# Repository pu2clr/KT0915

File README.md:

# [PU2CLR KT0915 Arduino Library](https://pu2clr.github.io/KT0915/)

This is an Arduino Library to control the KT0915 DSP receiver from KTMicro. The KT0915 is an integrated circuit that provides full band receiver on FM and AM (MW/SW/LW).

[Copyright (c) 2020 Ricardo Lima Caratti](https://pu2clr.github.io/KT0915#mit-license).

Contact: __pu2clr@gmail.com__.

__If you find this project useful, consider making a donation so that the author can purchase components and modules for improvements and testing of this library.__
[Click here to donate](https://www.paypal.com/donate/?business=LLV4PHKTXC4JW&no_recurring=0&item_name=Consider+making+a+donation.++So+I+can+purchase+components+and+modules+for+improvements+and+testing+of+this+library.&currency_code=USD)

## About Me

I hold a Master's degree in Educational Technology from the Federal University of Ceará, where I delved into the ways technology can enhance learning experiences. My passion for computer science led me to specialize in it, focusing on Distributed Systems Development with an Object-Oriented approach, at the University of Brasília. My academic journey began with a Bachelor's degree in Information Systems from the União Pioneira de Integração Social (UPIS-Brasília). Outside the classroom, my main hobbies are electronics and Amateur Radio. 

Be a member of Facebook group [DSP receivers for hobbyists](https://www.facebook.com/groups/2655942598067211)

## Donate 

If you find this project useful, consider making a donation so that the author of this library can purchase components and modules for improvements and testing of this library. [Click here to donate.](https://www.paypal.com/donate/?business=LLV4PHKTXC4JW&no_recurring=0&item_name=Consider+making+a+donation.++So+I+can+purchase+components+and+modules+for+improvements+and+testing+of+this+library.&currency_code=USD)

# Contents

1. [Preface](https://pu2clr.github.io/KT0915#preface)
2. [Your support is important](https://pu2clr.github.io/KT0915#your-support-is-important)
3. [Library Features](https://pu2clr.github.io/KT0915#library-features)
4. [MIT License](https://pu2clr.github.io/KT0915#mit-license)
5. [Library Installation](https://pu2clr.github.io/KT0915#library-installation)
6. [About KT0915 DSP radio](https://pu2clr.github.io/KT0915#about-kt0915-dsp-radio)
   * [KT0915 pinout](https://pu2clr.github.io/KT0915#kt0915-pinout)
7. [SCHEMATIC](https://pu2clr.github.io/KT0915#schematic)
8.  [API Documentation](https://pu2clr.github.io/KT0915/extras/docs/html/index.html)
9.  [Source code - Examples](https://github.com/pu2clr/KT0915/tree/master/examples)
10. [Videos](https://pu2clr.github.io/KT0915#videos)
11. [References](https://pu2clr.github.io/KT0915#references)

## Preface

The KT0915 is a full band AM (LW, MW and SW) and FM DSP receiver that can provide you a easy way to build a high quality radio with low cost. This device, will surprise hobbyists and experimenters with its simplicity.

In this document you will see Arduino source codes, schematics, examples and tips to help you to build a receiver based on Arduino board and the KT0915 device.  The project and examples shown here do not intend to be a real receiver for exigent listener. However, it is possible to start with it and after add some improvements. On the other hand, with the simple circuits shown here, the experimenter may be surprised with its performance.

{% include video01.html %}

[PU2CLR KT0915 Arduino LIbrary - AM (MW and SW) and FM receiver with KT0915](https://youtu.be/H6SwbuN3niU)

<BR>

{% include tutorial.html %}

[Video Tutorial](https://youtu.be/f3P6KL0XJpw)

## See also

* [PU2CLR Si4735 Library for Arduino](https://pu2clr.github.io/SI4735/). This library was built based on “Si47XX PROGRAMMING GUIDE; AN332” and it has support to FM, AM and SSB modes (LW, MW and SW). It also can be used on all members of the SI47XX family respecting, of course, the features available for each IC version;
* [PU2CLR SI4844 Arduino Library](https://pu2clr.github.io/SI4844). This is an Arduino library for the SI4844, BROADCAST ANALOG TUNING DIGITAL * DISPLAY AM/FM/SW RADIO RECEIVER,  IC from Silicon Labs.  It is available on Arduino IDE. This library is intended to provide an easier interface for controlling the SI4844.
* [PU2CLR AKC695X Arduino Library](https://pu2clr.github.io/AKC695X/). The AKC695X is a family of IC DSP receiver from AKC technology. The AKC6955 and AKC6959sx support AM and FM modes. On AM mode the AKC6955 and AKC6959sx work on LW, MW and SW. On FM mode they work from 64MHz to 222MHz.
* [PU2CLR KT0915 Arduino Library](https://pu2clr.github.io/KT0915/). The KT0915 is a full band AM (LW, MW and SW) and FM DSP receiver that can provide you a easy way to build a high quality radio with low cost.
* [PU2CLR BK108X](https://pu2clr.github.io/BK108X/). The BK1086 and BK1088 are DSP receivers from BAKEN. The BK1088 is a BROADCAST FM and AM (LW, MW and ) RECEIVER and BK1086 is a subset of the BK1088 (it does not have LW and SW acording to the Datasheet).
* [PU2CLR RDA5807 Arduino Library](https://pu2clr.github.io/RDA5807/). The RDA5807 is a FM DSP integrated circuit receiver (50 to 115MHz) with low noise amplifier support. This device requires very few external components if compared with other similar devices. It also supports RDS/RBDS functionalities, direct auto gain control (AGC) and real time adaptive noise cancellation function.
* [PU2CLR SI470X Arduino Library](https://pu2clr.github.io/SI470X/). It is a Silicon Labs device family that integrates the complete functionalities for FM receivers, including RDS (Si4703).
* [PU2CLR MCP23008](https://pu2clr.github.io/MCP23008/). It is an Arduino Library to control the MCP23008/MCP23S08 8-Bit I/O Expander. The MCP23008 device provides 8-bit, general purpose, parallel I/O expansion. It can be controlled via I2C bus applications. It is a great and inexpensive device that allow you to add more devices to be controlled by your Arduino board via I2C protocol.
* [PU2CLR - PCF8574 Arduino Library](https://pu2clr.github.io/PCF8574/). It is an Arduino Library to control the PCF8574 8-Bit I/O Expander. The PCF8574 device provides 8-bit, general purpose, parallel I/O expansion. It can be controlled via I²C bus applications. It is a great and inexpensive device that allow you to add more peripherals to be controlled by your Arduino board via I²C protocol.
* [QN8066 FM DSP RX/TX Arduino Library](https://github.com/pu2clr/QN8066). An easy-to-use interface for controlling the QN8066 FM transceiver and receiver.

### More Arduino Projects developed by author 

* [Multipurpose signal generator with SI5351](https://pu2clr.github.io/SI5351/). It is a multipurpose signal generator controlled by Arduino. This project uses the SI5351 from Silicon Labs. The Arduino sketch is configured to control the SI5351 with three channels from 32.768KHz to 160MHz and steps from 1Hz to 1MHz.
* [Shortwave Arduino Transmitter](https://pu2clr.github.io/Small-Shortwave-Transmitter/). This project is about a shortwave transmitter from 3 MHz to 30 MHz. It uses the SI5351 oscillator from Silicon Labs controlled by Arduino. Also, you can use it with a crystal oscillator. In this case, you will not need the SI5351 device and Arduino. 
* [Android and iOS Bluetooth Remote Control for PU2CLR Arduino Library DSP receivers](https://pu2clr.github.io/bluetooth_remote_control/). This project is an extension of the Arduino library projects for: [SI4735](https://pu2clr.github.io/SI4735/); [AKC6959](https://pu2clr.github.io/AKC695X/) and [KT0915](https://pu2clr.github.io/KT0915/). It is a simple example that shows a way to use your smartphone as a remote control via Bluetooth. In order to follow the steps presented here, I am assuming that you have some knowledge in development for mobile devices. Also, you will need to be familiar with the Javascript programming language. The development environment used by this project is the [Apache Cordova](https://cordova.apache.org/docs/en/latest/guide/overview/index.html). Cordova is a open-source mobile development framework that allows you to develop cross-platform applications. That means you can code once and deploy the application in many system, including iOS and Android. 
Cordova provides an easy way to develop for iOS and Android.  
* [Band Pass Filter controlled by Arduino](https://pu2clr.github.io/auto_bpf_arduino/). It is a HF band pass filter controlled by Arduino. It is designed for HF receivers. With this project, you can use a set of up to four HF bandpass filters that can be selected by Arduino. To do that you will need just two digital Arduino pins.

## Your support is important

If you would like to support this library development, consider joining this project via Github. Alternatively, make suggestions on new features and report errors if you find them. Thank you!

## Library Features

This library uses the I²C communication protocol and implements most of the functions offered by the KT0915 (BROADCAST AM / FM / SW / LW RECEIVER).

The main features of this library are listed below.

1. Open Source. It is free. You can use, copy, modify, merge, publish, distribute, sublicense, and/or sell copies of the Software. See [MIT License to know more](https://pu2clr.github.io/AKC695X/#mit-license);
2. Built based on [KT0915 stereo FM / TV / MW / SW / LW digital tuning radio](http://maximradio.altervista.org/akc6955/AKC6955-datasheet-english.pdf);
3. C++ Language and Object-oriented programming. You can easily extend the AKC695X class by adding more functionalities;
4. Available on Arduino IDE (via Manage Libraries). Easy to install and use;
5. Cross-platform. You can compile and run this library on most of board available on Arduino IDE (Examples: ATtiny85, boards based on ATmega328 and ATmega-32u4, ATmega2560, ARM Cortex, STM32, Arduino DUE, ESP32 and more);
6. Simplifies projects based on KT0915 IC;
7. Support to 32.768KHz and external reference clock;
8. Support to audio controlled by the MCU (Arduino)  or potentiometer;
9.  Real time FM stereo or mono indicator;
10. FM stereo or mono selecting;
11. Real time signal level reading;
12. Real time AM and FM carrier to noise ratio information (dB).
13. Bandwidth selection for AM;
14. Custom band support;
15. More than 40 functions implemented.

## MIT License

Copyright (c) 2019 Ricardo Lima Caratti

Permission is hereby granted, free of charge, to any person obtaining a copy of this software and associated documentation files (the "Software"), to deal in the Software without restriction, including without limitation the rights to use, copy, modify, merge, publish, distribute, sublicense, and/or sell copies of the Software, and to permit persons to whom the Software is furnished to do so, subject to the following conditions:

The above copyright notice and this permission notice shall be included in all copies or substantial portions of the Software.

THE SOFTWARE IS PROVIDED "AS IS", WITHOUT WARRANTY OF ANY KIND, EXPRESS OR IMPLIED, INCLUDING BUT NOT LIMITED TO THE ARRANTIES OF MERCHANTABILITY, FITNESS FOR A PARTICULAR PURPOSE AND NONINFRINGEMENT. IN NO EVENT SHALL THE AUTHORS OR COPYRIGHT HOLDERS BE LIABLE FOR ANY CLAIM, DAMAGES OR OTHER LIABILITY, WHETHER IN AN ACTION OF CONTRACT, TORT OR OTHERWISE, ARISING FROM, OUT OF OR IN CONNECTION WITH THE SOFTWARE OR THE USE OR OTHER DEALINGS IN THE SOFTWARE.

<BR>

## Library Installation

You can install this library on your Arduino environment using different methods. The best ways to do that are described below.  

{% include libinstalling.html %}

### Installing via Arduino IDE

// TODO

## About KT0915 DSP radio

According to __"Monolithic Digital FM/MW/SW/LW Receiver Radio on a Chip(TM); KT0915"__ document from KTMicro, "the KT0915 is a fully integrated full band AM/FM digital radio receiver IC with patented technologies that offer full band FM/MW/SW/LW functionality, high quality audio performance, simple design and low BOM cost.
The direct frequency and volume control interface help custumers to maintain the classic looks of their existing products.

Thanks to the patented tuning technology, the receiver maintains good signal reception with short antenna. The chip consumes only 22mA current and can be powered by 2 AAA batteries. Another useful feature is that the volume and channel setup can be preserved in standby mode without external memories. KT0915 supports a wide range of reference clocks from 32.768KHz to 26MHz, hence can share system clocks with a varieties of MCUs further reducing the system BOM cost.

With high audio performance, fully integrated features and low BOM cost, KT0915 is ideal for various FM/MW/SW/LW applications and products".

### KT0915 features

1. Worldwide full band FM/MW/SW/LW support FM: 32MHz-110MHz
   * FM: 32MHz-110MHz
   * MW: 500KHz-1710KHz 
   * SW: 1.6MHz~32MHz 
   * LW: 150KHz ~ 280KHz
2. Fully integrated frequency synthesizer with no external component
3. High Sensitivity
   * 1.6uVEMF for FM
   * 16uVEMF for AM
4. High Fidelity
   * SNR (FM/AM): 60dB/55dB
   * THD: 0.3%
5. Low supply voltage: 2.2V to 3.6V, can be supplied by 2 AAA batteries
6. Automatic antenna tuning
7. Adjustable AM channel filters (2k/4k/6KHz)
8. Embedded FM SNR meter
9.  Fast seek/Tune
10. Integrated stereo headphone driver I²C control interface for MCU
11. Support traditional dial and digital key for frequency tuning and volume control
12. Memorize channel and volume in standby mode
13. Low Supply Current - 22mA (operating) <15uA (standby)
14. Support both 32.768KHz and 38KHz crystal
15. Support continuous reference frequency from 32.768KHz to 26MHz

Source: __"Monolithic Digital FM/MW/SW/LW Receiver Radio on a Chip(TM); KT0915"__ document from KTMicro

### KT0915 Pinout

 | Pin Number  | Pin Name  | Description |
 | ----------  | --------  | ----------- |
 | 1           | CH        | Channel Adjustment. Used to deal with mechanical tune option |
 | 2           | DVSS      | Digital Ground |
 | 3           | ROUT      | Righ channel audio output |
 | 4           | LOUT      | Left channel audio output |
 | 5           | AVSS      | Analog ground |
 | 6           | AVDD      | Power Supply |
 | 7           | XI/RCLK   | Crystal input or reference clock input setup |
 | 8           | XO        | Crystal Output |
 | 9           | ENABLE    | Chip enable. Tied to an internal 600kohm pull down resistor |
 | 10          | AMINN     | AM RF negative input |
 | 11          | AMINP     | AM RF positive input |
 | 12          | RFINP     | FM RF input |
 | 13          | RFGND     | RF ground |
 | 14          | SCL       | SCL of I²C bus. Tied to an internal 47kohm pull-up resistor |
 | 15          | SDA       | SDA of I²C bus. Tied to an internal 47kohm pull-up resistor |
 | 16          | VOL       | Volume adjustment. Used to deal with mechanical volume control |

### KT0915 SSOP16L package

#### About the Pin 1 (CH) and Pin 16 (VOL)

The KT0915 can be configured to deal with mechanical tuning via a variable resistors. For example, you can use a variable resistor to control the audio volume and another to tuninig the receiver. This resource is  enabled by setting the internal register GPIOCFG (Address 0x1D) of the device. The dial can be a variable resistor with the tap connected to CH and VOL as well. The divided voltage at the tap is processed by the internal KT0915  analog to digital converter (ADC). Finally, the converted datas are stored into the internal registers of the KT0915 device.

By default, this library the tune and volume are conttrolled by the MCU (Arduino). However, you can sets the mechanical feature by calling setTuneDialModeOn and setVolumeDialModeOn. See [API Documentation](https://pu2clr.github.io/KT0915/extras/docs/html/index.html).

See [KT0915 - Monolithic Digital FM/MW/SW/LW ReceiverRadio-on-a-Chip™](http://aitendo3.sakura.ne.jp/aitendo_data/product_img/ic/radio/KT0915%20/KT0915_datasheet_V022_aitendo.pdf); pages: 8, 9, 10 and 20.

## SCHEMATIC

You can use the Typical Application Circuit suggested by the KTMicro. This circuit can be found in the document KT0915-Monolithic Digital FM/MW/SW/LW Receiver Radio-on-a-Chip.  The main porpuse of this prototype below is testing de KT0915 Arduino Library. It does not intend to be a real radio for exigent listener. However, it is possible to start with it and after include some devices to improve, for example,  its sensibility beyond other desired features.  The schematic below does not use the ferrite antenna as suggested by KTMicro and no front-en as well.  See [KT0915 - Monolithic Digital FM/MW/SW/LW ReceiverRadio-on-a-Chip™](http://aitendo3.sakura.ne.jp/aitendo_data/product_img/ic/radio/KT0915%20/KT0915_datasheet_V022_aitendo.pdf); page 24.

<BR>

<BR>

__The KT0915 is a 3.3V part. If you are not using a 3.3V version of Arduino, you have to use a kind of 5V to 3.3V bidirectional converter. It is important to say that just power the KT0915 device with 3.3V from Arduino board is not enough. You have to be aware that the Arduino that operates with 5V, the digital pins and the I²C bus will send 5V signals to the KT0915 device. That configuration can make the system unstable or damage the device__.  

### Parts

The table below shows the component parts used to build the receiver prototype based on KT0915

<BR>

| Components |  Value    | Description |
| ---------- |  -------- | ----------- |
|    C1      |  10uF     | Ceramic or tantalum capacitor |
|    C2      |  100nF    | Ceramic or tantalum capacitor |
|   C3, C4   |  22pF     | Supply decoupling capacitor - Ceramic or tantalum capacitor |
|   C5, C6   |  10uF     | Electrolytic or tantalum capacitor |
|    C7      |  100nF    | AC coupling capacitor |  
|    Q1      | 32.768KHz | Crystal |
|   R1, R2   |  10K      | I²C buss Pull up ristors |
|   Arduino  | Pro Mini  | 3.3V 8Mhz |
|   KT0915   | DSP       | FM and AM receiver |
|    VCC     | 3.3V      | Baterry |

<BR>

## Photos

<BR>

<BR>

## Videos

[PU2CLR KT0915 Arduino LIbrary - First Test](https://youtu.be/H6SwbuN3niU)
[PU2CLR KT0915 Arduino Library - Sound testing](https://youtu.be/L3R1hmw8tqg)

## References

* [KT0915 - Monolithic Digital FM/MW/SW/LW ReceiverRadio-on-a-Chip™](http://aitendo3.sakura.ne.jp/aitendo_data/product_img/ic/radio/KT0915%20/KT0915_datasheet_V022_aitendo.pdf)
* [Radio, yes AM-SW-FM radio by DSP radio chip](https://hackaday.io/project/12944-radio-yes-am-sw-fm-radio-by-dsp-radio-chip)
* [KT0915_DSP_RADIO-fullscreen-info](https://github.com/kodera2t/KT0915_DSP_RADIO-fullscreen-info)
* [KT0915 Arduino](https://easyeda.com/wolfezrawilliam/KT0915-Arduino)

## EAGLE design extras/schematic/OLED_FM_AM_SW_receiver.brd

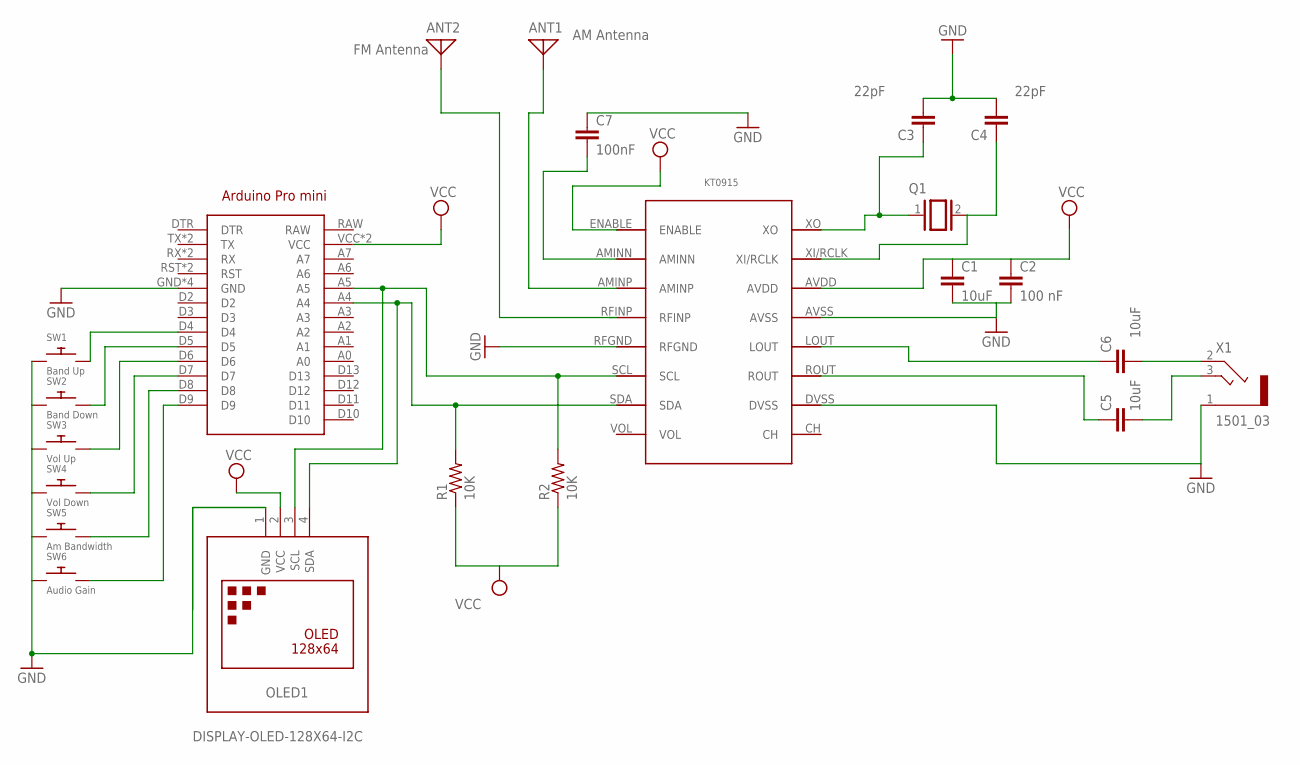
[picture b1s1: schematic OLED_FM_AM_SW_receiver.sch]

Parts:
ANT1: AM Antenna; PAD-01
ANT2: FM Antenna; PAD-01
ARDUINO1: ProMini 3.3v 8MHz; ARDUINO_PRO_MINI
C1: 10uF; 0603
C2: 100 nF; C1825K
C3, C4: 22pF; C1825K
C5, C6: 10uF; C1825K
C7: 100nF; C1825K
KT0915: KT0915
OLED1: DISPLAY-OLED-128X64-I2C
Q1: XTAL; Q
R1, R2: 10K; 0805-THM
SW1: Band Up; TACT_PANA-EVQ
SW2: Band Down; TACT_PANA-EVQ
SW3: Vol Up; TACT_PANA-EVQ
SW4: Vol Down; TACT_PANA-EVQ
SW5: Am Bandwidth; TACT_PANA-EVQ
SW6: Audio Gain; TACT_PANA-EVQ
X1: 1501_03

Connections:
GND: ARDUINO1.GND, ARDUINO1.GND@1 (GND), ARDUINO1.GND@2 (GND), ARDUINO1.GND@3 (GND), C1.2, C2.2, C3.2, C4.2, C7.1, KT0915.AVSS, KT0915.DVSS, KT0915.RFGND, X1.1
unnamed: ARDUINO1.D4, SW1.P$2
unnamed: ARDUINO1.A4, KT0915.SDA, OLED1.4 (SDA), R1.2
unnamed: ARDUINO1.A5, KT0915.SCL, OLED1.3 (SCL), R2.2
unnamed: C4.1, KT0915.XI/RCLK, Q1.2
unnamed: C3.1, KT0915.XO, Q1.1
unnamed: C6.1, KT0915.LOUT
unnamed: C6.2, X1.2
unnamed: C5.2, X1.3
unnamed: C7.2, KT0915.AMINN
unnamed: ARDUINO1.D5, SW2.P$2
unnamed: ANT1.1, KT0915.AMINP
unnamed: ANT2.1, KT0915.RFINP
unnamed: ARDUINO1.D7, SW4.P$2
unnamed: ARDUINO1.D6, SW3.P$2
unnamed: ARDUINO1.D8, SW5.P$2
unnamed: ARDUINO1.D9, SW6.P$2
unnamed: OLED1.1 (GND), SW1.P$1, SW2.P$1, SW3.P$1, SW4.P$1, SW5.P$1, SW6.P$1
unnamed: C5.1, KT0915.ROUT
VCC: ARDUINO1.VCC, ARDUINO1.VCC@1 (VCC), C1.1, C2.1, KT0915.AVDD, KT0915.ENABLE, OLED1.2 (VCC), R1.1, R2.1

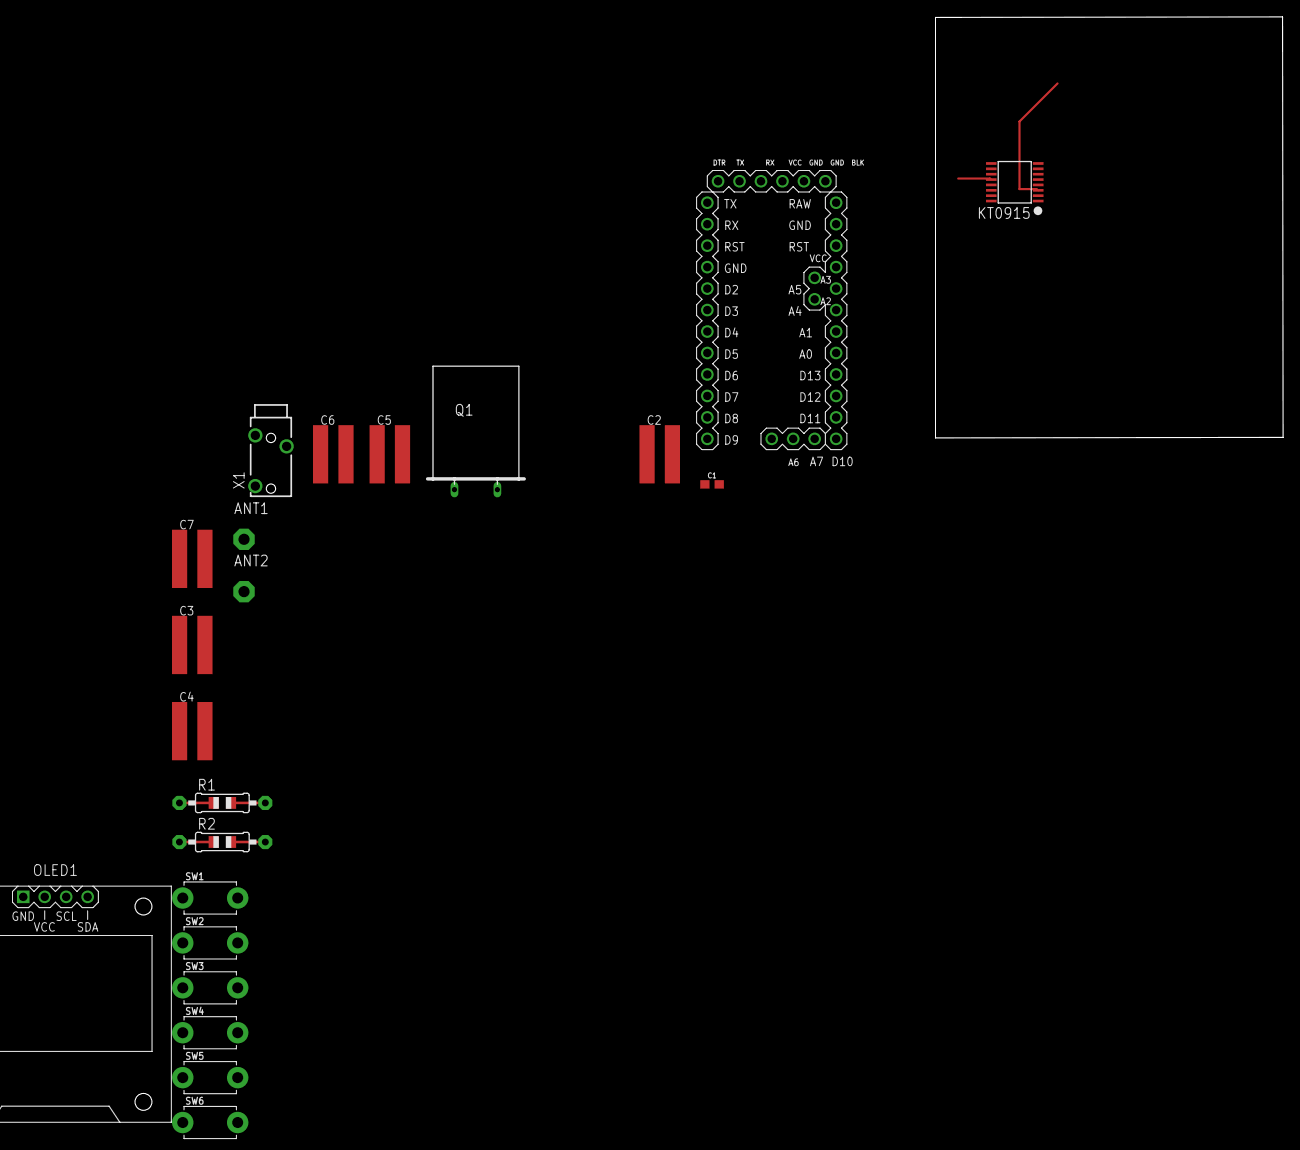
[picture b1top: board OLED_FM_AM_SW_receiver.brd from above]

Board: 2 copper layers, 41.1 x 49.8 mm, 22 parts (0 on the bottom side), 20 nets.

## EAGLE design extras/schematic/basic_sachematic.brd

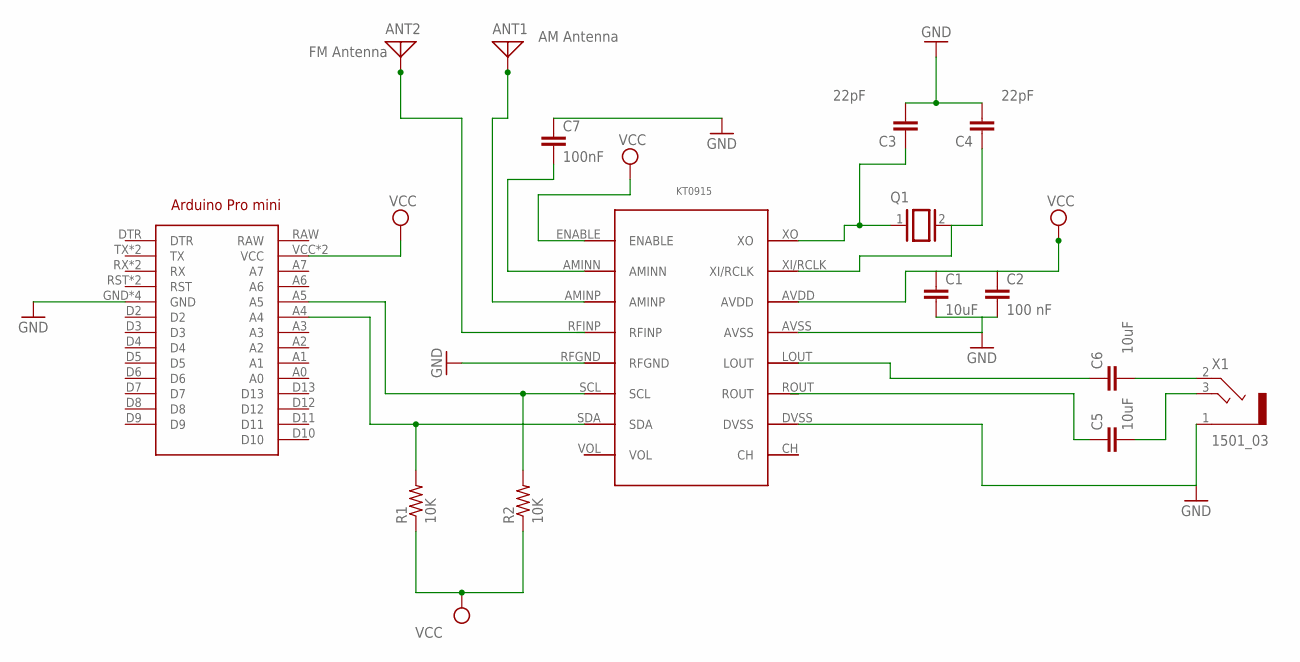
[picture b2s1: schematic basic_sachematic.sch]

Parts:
ANT1: AM Antenna; PAD-01
ANT2: FM Antenna; PAD-01
ARDUINO1: ARDUINO_PRO_MINI
C1: 10uF; 0603
C2: 100 nF; C1825K
C3, C4: 22pF; C1825K
C5, C6: 10uF; C1825K
C7: 100nF; C1825K
KT0915: KT0915
Q1: XTAL; Q
R1, R2: 10K; 0805-THM
X1: 1501_03

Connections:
GND: ARDUINO1.GND, ARDUINO1.GND@1 (GND), ARDUINO1.GND@2 (GND), ARDUINO1.GND@3 (GND), C1.2, C2.2, C3.2, C4.2, C7.1, KT0915.AVSS, KT0915.DVSS, KT0915.RFGND, X1.1; also elsewhere on the board
unnamed 1: ARDUINO1.A4, KT0915.SDA, R1.2; also elsewhere on the board
unnamed 2: ARDUINO1.A5, KT0915.SCL, R2.2; also elsewhere on the board
unnamed 3: C4.1, KT0915.XI/RCLK, Q1.2; also elsewhere on the board
unnamed 4: C3.1, KT0915.XO, Q1.1; also elsewhere on the board
unnamed 5: C6.1, KT0915.LOUT; also elsewhere on the board
unnamed: C6.2, X1.2
unnamed: C5.2, X1.3
unnamed 8: C7.2, KT0915.AMINN; also elsewhere on the board
unnamed 9: ANT1.1, KT0915.AMINP; also elsewhere on the board
unnamed 10: ANT2.1, KT0915.RFINP; also elsewhere on the board
unnamed 11: C5.1, KT0915.ROUT; also elsewhere on the board
VCC: ARDUINO1.VCC, ARDUINO1.VCC@1 (VCC), C1.1, C2.1, KT0915.AVDD, KT0915.ENABLE, R1.1, R2.1; also elsewhere on the board

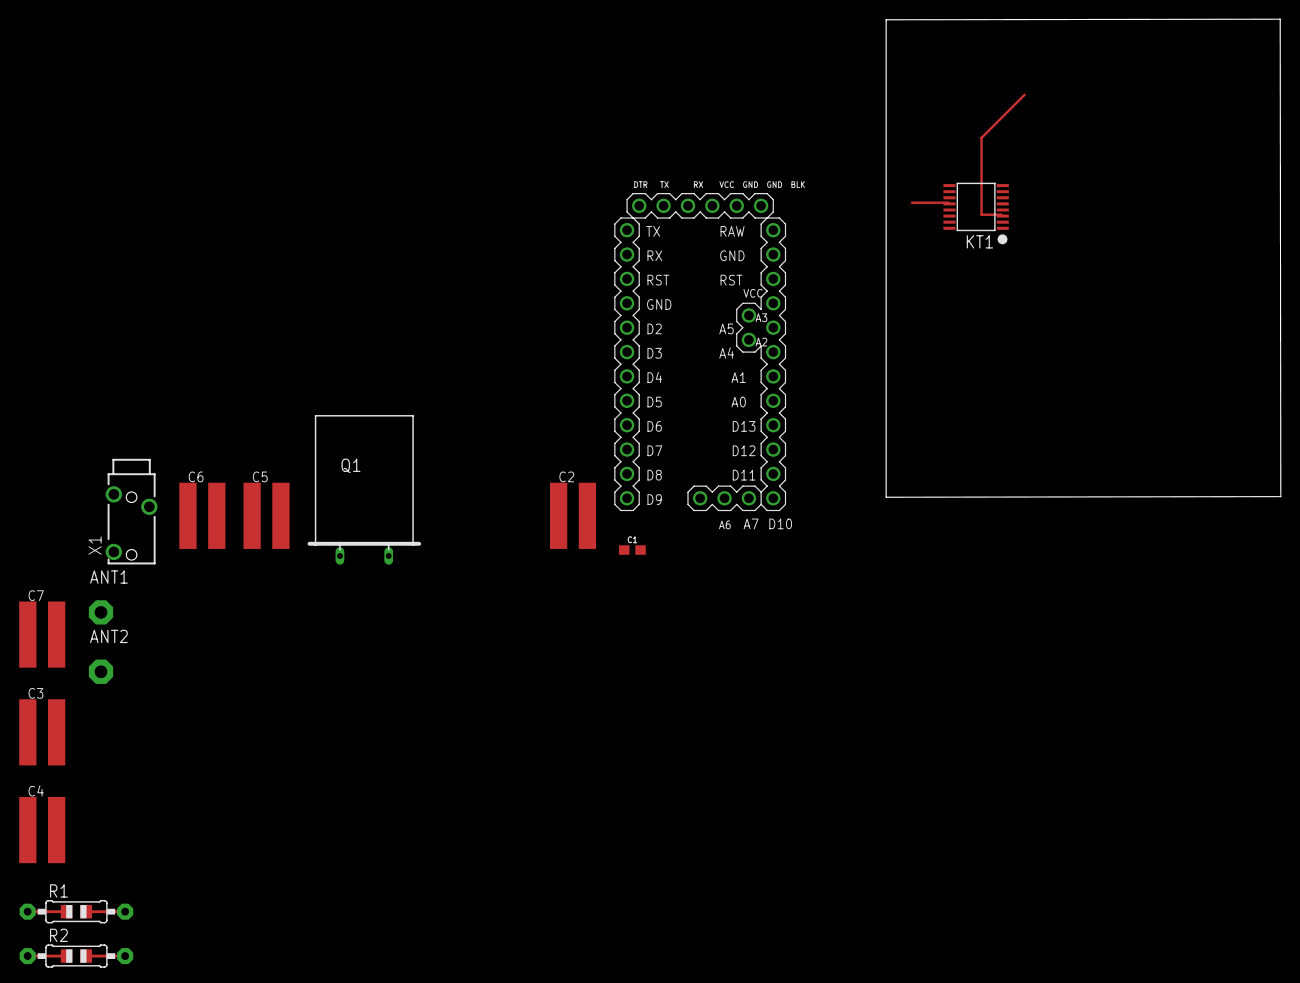
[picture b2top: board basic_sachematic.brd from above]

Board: 2 copper layers, 41.1 x 49.8 mm, 15 parts (0 on the bottom side), 13 nets.

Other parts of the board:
KT1: KT0915

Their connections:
GND: KT1.AVSS, KT1.DVSS, KT1.RFGND; also elsewhere on the board
unnamed 1: KT1.SDA; also elsewhere on the board
unnamed 2: KT1.SCL; also elsewhere on the board
unnamed 3: KT1.XI/RCLK; also elsewhere on the board
unnamed 4: KT1.XO; also elsewhere on the board
unnamed 5: KT1.LOUT; also elsewhere on the board
unnamed 8: KT1.AMINN; also elsewhere on the board
unnamed 9: KT1.AMINP; also elsewhere on the board
unnamed 10: KT1.RFINP; also elsewhere on the board
unnamed 11: KT1.ROUT; also elsewhere on the board
VCC: KT1.AVDD, KT1.ENABLE; also elsewhere on the board

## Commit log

2020-06-02 Starting
    Starting
2020-06-02 KT0915 Arduino Library
2020-06-02 Documentation
2020-06-03 Set theme jekyll-theme-cayman
2020-06-03 Extras
2020-06-03 Examples
2020-06-04 KT0915
2020-06-04 KT0915Arduino Library
2020-06-04 Set theme jekyll-theme-slate
2020-06-04 Set theme jekyll-theme-merlot
2020-06-17 Library Properties
2020-06-25 Contributing
2021-03-13 Set theme jekyll-theme-hacker

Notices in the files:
parts and their libraries:
SparkFun-Capacitors: Licensing: Creative Commons ShareAlike 4.0 International - https://creativecommons.org/licenses/by-sa/4.0
diy-modules: Released under the Creative Commons Attribution 4.0 International License: http://creativecommons.org/licenses/by/4.0
